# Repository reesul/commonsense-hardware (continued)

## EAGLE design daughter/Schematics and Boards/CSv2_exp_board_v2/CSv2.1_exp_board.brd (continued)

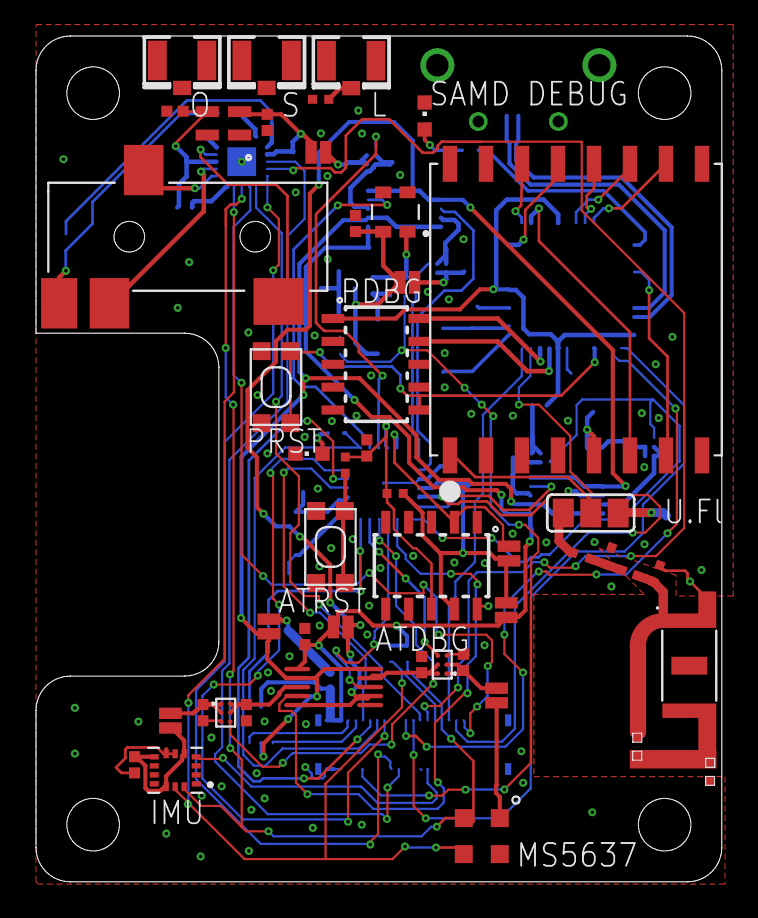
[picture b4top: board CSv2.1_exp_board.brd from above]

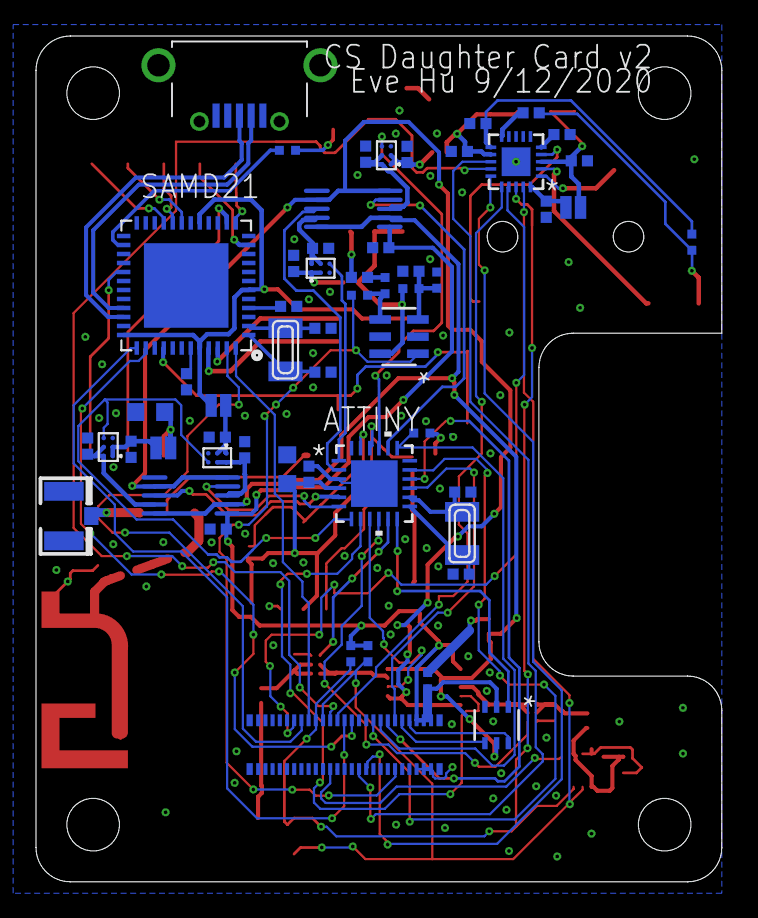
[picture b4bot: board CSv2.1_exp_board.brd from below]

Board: 2 copper layers, 38.1 x 47.0 mm, 103 parts (56 on the bottom side), 98 nets.

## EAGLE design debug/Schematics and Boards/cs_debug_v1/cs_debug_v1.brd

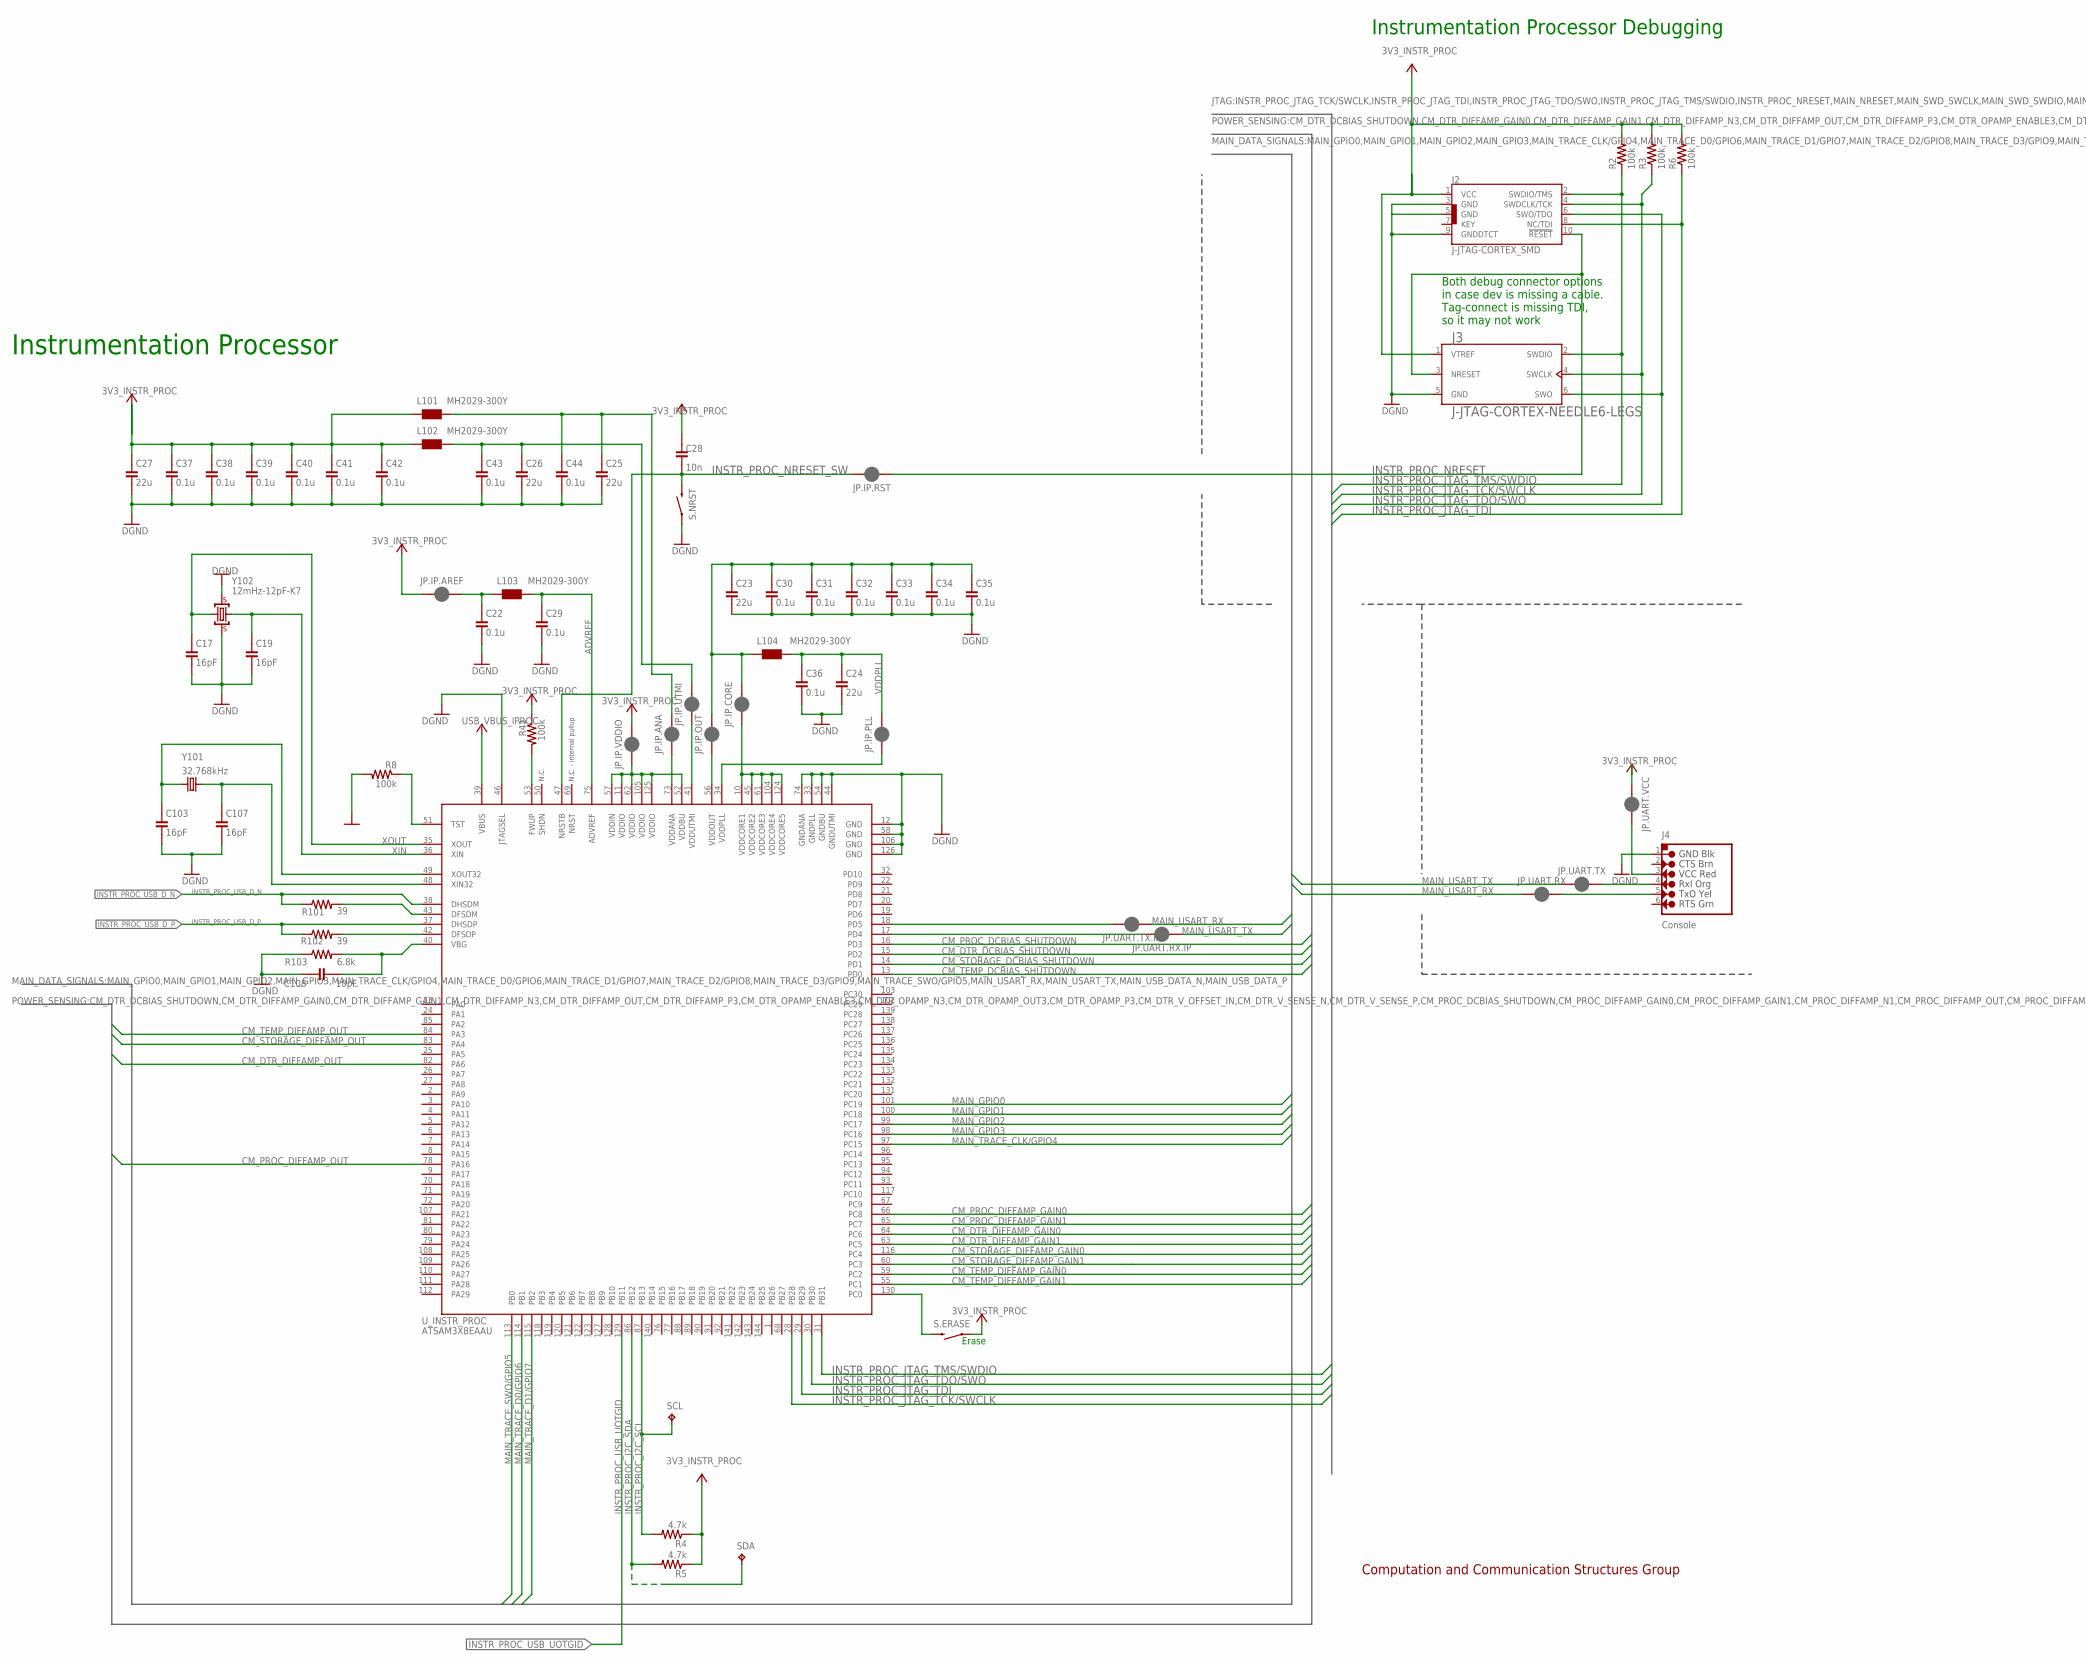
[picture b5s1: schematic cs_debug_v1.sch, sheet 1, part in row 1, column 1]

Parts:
C17, C19, C103, C107: 16pF; C0603; MPN C0603C160J5GACTU
C22, C29, C30, C31, C32, C33, C34, C35, C36, C37, C38, C39, C40, C41, C42, C43, C44: 0.1u; C0402; VOLTAGE 10V; MPN C0402C104K8RACTU
C23, C24, C25, C26, C27: 22u; C0805; VOLTAGE 10V; MPN C0805C226M8PAC7800
C28: 10n; C0402; MPN C0402C103K8RACTU
C108: 10pF; C0603; MPN C0603C100K8RAC7867
J2: J-JTAG-CORTEX_SMD; SAMTECH_FTSH-105-01; PART_NO FTSH-105-01-L-DV-K-TR
J3: J-JTAG-CORTEX-NEEDLE6-LEGS; 8.06.16_6-PIN_NEEDLE_ADAPTER_LEGS
J4: J-SERIAL-PORT; HEADER-1X6; PART_NO PH1-06-UA
JP.IP.ANA, JP.IP.AREF, JP.IP.CORE, JP.IP.OUT, JP.IP.PLL, JP.IP.RST, JP.IP.UTMI, JP.IP.VDDIO, JP.UART.RX, JP.UART.RX.IP, JP.UART.TX, JP.UART.TX.IP, JP.UART.VCC: JUMPER-SMT_2_NC_PASTE_NO-SILK; SMT-JUMPER_2_NC_PASTE_NO-SILK
L101, L102, L103, L104: MH2029-300Y; L0805; PART_NO MH2029-300Y
R2, R3, R6: 100k; R0402; MPN ERJ-2GEJ104X
R4, R5: 4.7k; R0402; MPN ERJ-2GEJ472X
R8, R41: 100k; R0402; MPN RC0402JR-07100KL
R101, R102: 39; R0402; MPN ERJ-2GEJ390X
R103: 6.8k; R0402; MPN ERJ-2GEJ682X
S.ERASE, S.NRST: Momentary; SW_EVQ-P7L01P; MPN EVQP7L01P
SCL: TPTP10SQ; TP10SQ
SDA: TPTP10SQ; TP10SQ
U_INSTR_PROC: ATSAM3X8EA-AU; LQFP144; MPN ATSAM3X8EAAU
Y101: 32.768kHz; CRYSTAL-SMD-3.2X1.5MM; MPN ECS-.327-12.5-34B-TR
Y102: 12mHz-12pF-K7; CRYSTAL-3.2-2.5; MPN ABM8G-12.000MHZ-4Y-T3

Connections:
3V3_INSTR_PROC: C27.1, C28.1, C37.1, C38.1, C39.1, C40.1, C41.1, C42.1, J2.1 (VCC), J3.1 (VTREF), JP.IP.AREF.1, JP.IP.VDDIO.2, JP.UART.VCC.1, L101.1, L102.1, R2.2, R3.2, R4.1, R5.1, R6.2, R41.1, S.ERASE.1_1 (1), S.ERASE.1_2 (1); also elsewhere on the board
ADVREF: C29.1, L103.2, U_INSTR_PROC.75 (ADVREF)
ADVREF_PRE: C22.1, JP.IP.AREF.2, L103.1
CM_DTR_DCBIAS_SHUTDOWN: U_INSTR_PROC.15 (PD2); also elsewhere on the board
CM_DTR_DIFFAMP_GAIN0: U_INSTR_PROC.64 (PC6); also elsewhere on the board
CM_DTR_DIFFAMP_GAIN1: U_INSTR_PROC.63 (PC5); also elsewhere on the board
CM_DTR_DIFFAMP_OUT: U_INSTR_PROC.82 (PA6); also elsewhere on the board
CM_PROC_DCBIAS_SHUTDOWN: U_INSTR_PROC.16 (PD3); also elsewhere on the board
CM_PROC_DIFFAMP_GAIN0: U_INSTR_PROC.66 (PC8); also elsewhere on the board
CM_PROC_DIFFAMP_GAIN1: U_INSTR_PROC.65 (PC7); also elsewhere on the board
CM_PROC_DIFFAMP_OUT: U_INSTR_PROC.78 (PA16); also elsewhere on the board
CM_STORAGE_DCBIAS_SHUTDOWN: U_INSTR_PROC.14 (PD1); also elsewhere on the board
CM_STORAGE_DIFFAMP_GAIN0: U_INSTR_PROC.116 (PC4); also elsewhere on the board
CM_STORAGE_DIFFAMP_GAIN1: U_INSTR_PROC.60 (PC3); also elsewhere on the board
CM_STORAGE_DIFFAMP_OUT: U_INSTR_PROC.83 (PA4); also elsewhere on the board
CM_TEMP_DCBIAS_SHUTDOWN: U_INSTR_PROC.13 (PD0); also elsewhere on the board
CM_TEMP_DIFFAMP_GAIN0: U_INSTR_PROC.59 (PC2); also elsewhere on the board
CM_TEMP_DIFFAMP_GAIN1: U_INSTR_PROC.55 (PC1); also elsewhere on the board
CM_TEMP_DIFFAMP_OUT: U_INSTR_PROC.84 (PA3); also elsewhere on the board
DGND: C17.2, C19.2, C22.2, C23.2, C24.2, C25.2, C26.2, C27.2, C29.2, C30.2, C31.2, C32.2, C33.2, C34.2, C35.2, C36.2, C37.2, C38.2, C39.2, C40.2, C41.2, C42.2, C43.2, C44.2, C103.2, C107.2, C108.2, J2.3 (GND), J2.5 (GND), J2.9 (GNDDTCT), J3.5 (GND), J4.1 (GND), R8.2, R103.1, S.NRST.1_1 (1), S.NRST.1_2 (1), U_INSTR_PROC.12 (GND), U_INSTR_PROC.33 (GNDPLL), U_INSTR_PROC.44 (GNDUTMI), U_INSTR_PROC.46 (JTAGSEL), U_INSTR_PROC.54 (GNDBU), U_INSTR_PROC.58 (GND), U_INSTR_PROC.74 (GNDANA), U_INSTR_PROC.106 (GND), U_INSTR_PROC.126 (GND), Y102.2 (GND), Y102.4 (GND); also elsewhere on the board
ERASE_S: S.ERASE.2_1 (2), S.ERASE.2_2 (2), U_INSTR_PROC.130 (PC0)
FWUP: R41.2, U_INSTR_PROC.53 (FWUP)
INSTR_PROC_I2C_SCL: R4.2, SCL.TP, U_INSTR_PROC.87 (PB13); also elsewhere on the board
INSTR_PROC_I2C_SDA: R5.2, SDA.TP, U_INSTR_PROC.86 (PB12); also elsewhere on the board
INSTR_PROC_JTAG_TCK/SWCLK: J2.4 (SWDCLK/TCK), J3.4 (SWCLK), R3.1, U_INSTR_PROC.28 (PB28)
INSTR_PROC_JTAG_TDI: J2.8 (NC/TDI), R6.1, U_INSTR_PROC.29 (PB29)
INSTR_PROC_JTAG_TDO/SWO: J2.6 (SWO/TDO), J3.6 (SWO), U_INSTR_PROC.30 (PB30)
INSTR_PROC_JTAG_TMS/SWDIO: J2.2 (SWDIO/TMS), J3.2 (SWDIO), R2.1, U_INSTR_PROC.31 (PB31)
INSTR_PROC_NRESET: J2.10 (!RESET), J3.3 (NRESET), JP.IP.RST.1
INSTR_PROC_NRESET_SW: C28.2, JP.IP.RST.2, S.NRST.2_1 (2), S.NRST.2_2 (2), U_INSTR_PROC.47 (NRSTB)
INSTR_PROC_USB_D_N: R101.1, U_INSTR_PROC.38 (DHSDM); also elsewhere on the board
INSTR_PROC_USB_D_P: R102.1, U_INSTR_PROC.37 (DHSDP); also elsewhere on the board
INSTR_PROC_USB_UOTGID: U_INSTR_PROC.129 (PB11)
MAIN_GPIO0: U_INSTR_PROC.101 (PC19); also elsewhere on the board
MAIN_GPIO1: U_INSTR_PROC.100 (PC18); also elsewhere on the board
MAIN_GPIO2: U_INSTR_PROC.99 (PC17); also elsewhere on the board
MAIN_GPIO3: U_INSTR_PROC.98 (PC16); also elsewhere on the board
MAIN_TRACE_CLK/GPIO4: U_INSTR_PROC.97 (PC15); also elsewhere on the board
MAIN_TRACE_D0/GPIO6: U_INSTR_PROC.114 (PB1); also elsewhere on the board
MAIN_TRACE_D1/GPIO7: U_INSTR_PROC.115 (PB2); also elsewhere on the board
MAIN_TRACE_SWO/GPIO5: U_INSTR_PROC.113 (PB0); also elsewhere on the board
MAIN_USART_RX: JP.UART.RX.1, JP.UART.TX.IP.1; also elsewhere on the board
MAIN_USART_TX: JP.UART.RX.IP.1, JP.UART.TX.1; also elsewhere on the board
unnamed: R102.2, U_INSTR_PROC.42 (DFSDP)
unnamed: JP.UART.TX.IP.2, U_INSTR_PROC.18 (PD5)
unnamed: JP.UART.RX.IP.2, U_INSTR_PROC.17 (PD4)
unnamed: J4.4 (RX-I), JP.UART.TX.2
unnamed: J4.5 (TX-O), JP.UART.RX.2
unnamed: J4.3 (VCC-I), JP.UART.VCC.2
unnamed: R101.2, U_INSTR_PROC.43 (DFSDM)
TST: R8.1, U_INSTR_PROC.51 (TST)
USB_VBUS_IPROC: U_INSTR_PROC.39 (VBUS); also elsewhere on the board
VBG: C108.1, R103.2, U_INSTR_PROC.40 (VBG)
VDDANA1: C25.1, C44.1, JP.IP.ANA.2, L101.2
VDDANA_0: JP.IP.ANA.1, U_INSTR_PROC.73 (VDDANA)
VDDIO1: JP.IP.VDDIO.1, U_INSTR_PROC.11 (VDDIO), U_INSTR_PROC.52 (VDDBU), U_INSTR_PROC.57 (VDDIN), U_INSTR_PROC.62 (VDDIO), U_INSTR_PROC.105 (VDDIO), U_INSTR_PROC.125 (VDDIO)
VDDOUT: C23.1, C30.1, C31.1, C32.1, C33.1, C34.1, C35.1, JP.IP.CORE.2, JP.IP.OUT.2, L104.1
VDDOUTMI: C26.1, C43.1, JP.IP.UTMI.2, L102.2
VDDOUTMI_0: JP.IP.UTMI.1, U_INSTR_PROC.41 (VDDUTMI)
VDDOUT_0: JP.IP.OUT.1, U_INSTR_PROC.56 (VDDOUT)
VDDOUT_1: JP.IP.CORE.1, U_INSTR_PROC.10 (VDDCORE1), U_INSTR_PROC.45 (VDDCORE2), U_INSTR_PROC.61 (VDDCORE3), U_INSTR_PROC.104 (VDDCORE4), U_INSTR_PROC.124 (VDDCORE5)
VDDPLL: C24.1, C36.1, JP.IP.PLL.2, L104.2
VDDPLL_0: JP.IP.PLL.1, U_INSTR_PROC.34 (VDDPLL)
XIN: C19.1, U_INSTR_PROC.36 (XIN), Y102.1 (C1)
XIN32: C107.1, U_INSTR_PROC.48 (XIN32), Y101.P$1 (1)
XOUT: C17.1, U_INSTR_PROC.35 (XOUT), Y102.3 (C2)
XOUT32: C103.1, U_INSTR_PROC.49 (XOUT32), Y101.P$2 (2)

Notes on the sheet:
N.C.
N.C. - internal pullup
Instrumentation Processor
Computation and Communication Structures Group
Both debug connector options in case dev is missing a cable. Tag-connect is missing TDI, so it may not work
Instrumentation Processor Debugging
Erase

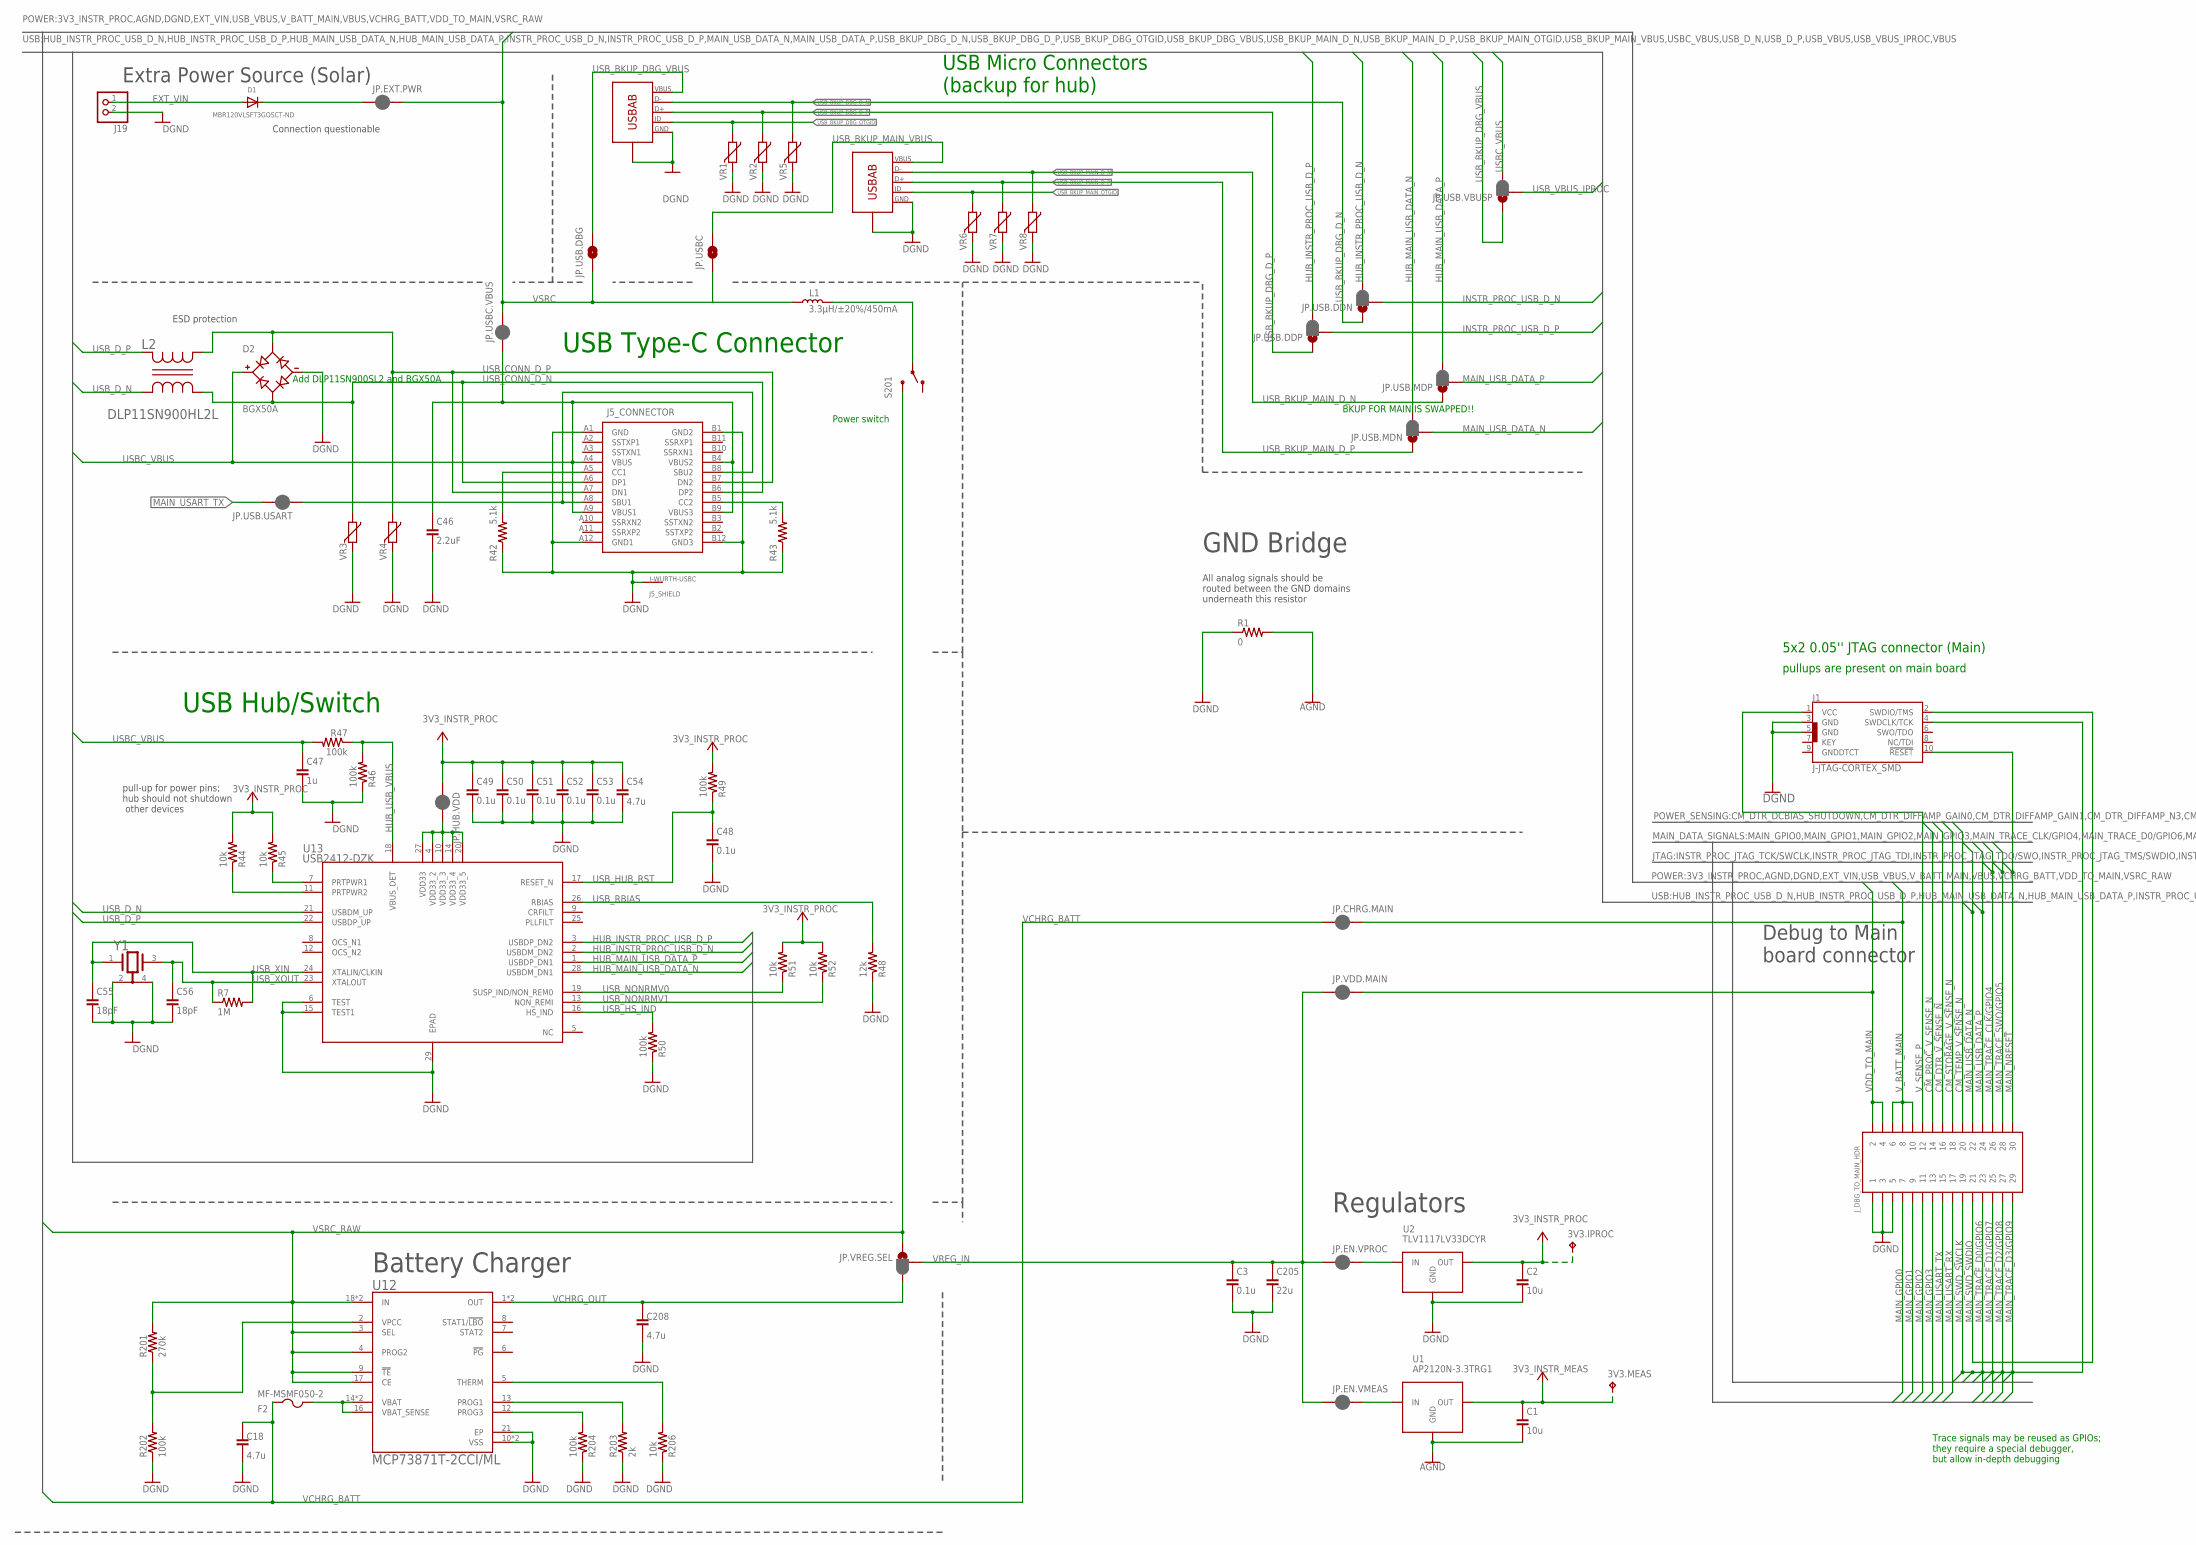
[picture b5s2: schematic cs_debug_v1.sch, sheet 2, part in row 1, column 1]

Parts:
3V3.IPROC, 3V3.MEAS: TPTP10SQ; TP10SQ
C1, C2: 10u; C0805; VOLTAGE 10V; MPN C0805C106M8RACTU
C3, C48, C49, C50, C51, C52, C53: 0.1u; C0402; VOLTAGE 10V; MPN C0402C104K8RACTU
C18, C54: 4.7u; C0402; MPN C0603C475M8PACTU
C46: 2.2uF; C0603; MPN C0603C225K8RACTU
C47: 1u; C0402; VOLTAGE 10V; MPN C0402C105K8PACTU
C55, C56: 18pF; C0402; MPN C0402C180J8GAC7867
C205: 22u; C0805; VOLTAGE 10V; MPN C0805C226M8PAC7800
C208: 4.7u; C0603; MPN C0603C475M8PACTU
D1: MBR120VLSFT3GOSCT-ND; SOD-123; MPN MBR120VLSFT3G
D2: BGX50A; SOT143_BGX50A
F2: MF-MSMF050-2; 1812; MPN MF-MSMF050-2
J1: J-JTAG-CORTEX_SMD; SAMTECH_FTSH-105-01; PART_NO FTSH-105-01-L-DV-K-TR
J5: J-WURTH-USBC; 632723X00011; PART_NO 632723100011
J19: Solar; JST-PH-2-SMT-RA; PART_NO S2B-PH-SM4-TB(LF)(SN)
J.USB.DBG, J.USB.MN: J-USB-HIROSE-MICRO-USB; USB-THRU-ZX62D-AB-5P8; MPN ZX62D-AB-5P8(30)
JP.CHRG.MAIN, JP.EN.VMEAS, JP.EN.VPROC, JP.EXT.PWR, JP.HUB.VDD, JP.USB.USART, JP.USBC.VBUS, JP.VDD.MAIN: JUMPER-SMT_2_NC_PASTE_NO-SILK; SMT-JUMPER_2_NC_PASTE_NO-SILK
JP.USB.DBG, JP.USBC: JUMPER-SMT_2_NO_PASTEFREE; SMT-JUMPER_2_NO_PASTEFREE_NO-SILK
JP.USB.DDN, JP.USB.DDP, JP.USB.MDN, JP.USB.MDP, JP.USB.VBUSP, JP.VREG.SEL: JUMPER-SMT_3_1-NC_PASTE_NO-SILK; SMT-JUMPER_3_1-NC_PASTE_NO-SILK
J_DBG_TO_MAIN_HDR: HIROSE-DF40_30-PIN_CONNECTORS-HEADER; HRS_DF40C-30DP-0.4V(51); MPN DF40C-30DP-0.4V(51)
L1: 3.3µH/±20%/450mA; 0805; MPN MLZ2012A3R3WT000
L2: DLP11SN900HL2L; IND_DLP11S_0504_MUR; MPN DLP11SN900HL2L
R1: 0; R2010; MPN ERJ-S1D0R00U
R7: 1M; R0402; MPN ERJ-U02J105X
R42, R43: 5.1k; R0603; MPN ERJ-3EKF5101V
R44, R45, R51, R52, R206: 10k; R0402; MPN ERJ-2GEJ103X
R46, R47, R49, R50, R202, R204: 100k; R0402; MPN ERJ-2GEJ104X
R48: 12k; R0402; MPN ERJ-2RKF1202X
R201: 270k; R0402; MPN ERJ-2GEJ274X
R203: 2k; R0402; MPN ERJ-2GEJ202X
S201: SLIDESWITCH-SPDT-SMD-RIGHT-ANGLE; SWITCH_SPST_SMD_A; PART_NO CUS-12TB
U1: AP2120N-3.3TRG1; SOT23-3_AP2120N; MPN AP2120N-3.3TRG1
U2: TLV1117LV33DCYR; DCY4
U12: MCP73871T-2CCI/ML; QFN50P400X400X100-21N; MPN MCP73871T-2CCI/ML
U13: USB2412-DZK; QFN28_5X5MC_MCH
VR1, VR2, VR3, VR4, VR5, VR6, VR7, VR8: VARISTOR; R0603; PART_NO CG0603MLC-05E
Y1: EPSON_TSX-3225_24.0000MF10Z-C3; XTAL_EPSON_TSX3225; MPN TSX-3225 24.0000MF10Z-C3

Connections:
3V3_INSTR_MEAS: 3V3.MEAS.TP, C1.1, U1.OUT; also elsewhere on the board
3V3_INSTR_PROC: 3V3.IPROC.TP, C2.1, C49.1, C50.1, C51.1, C52.1, C53.1, C54.1, JP.HUB.VDD.1, R44.2, R45.2, R49.2, R51.2, R52.2, U2.OUT, U2.OUT_TAB (OUT); also elsewhere on the board
AGND: C1.2, R1.2, U1.GND; also elsewhere on the board
BAT_CHG_PROG1: R203.2, U12.13 (PROG1)
CC3: J5.A5 (CC1), R42.2
CC4: J5.B5 (CC2), R43.2
CHG_VPCC: R201.1, R202.2, U12.2 (VPCC)
CM_DTR_V_SENSE_N: J_DBG_TO_MAIN_HDR.16; also elsewhere on the board
CM_PROC_V_SENSE_N: J_DBG_TO_MAIN_HDR.14; also elsewhere on the board
CM_STORAGE_V_SENSE_N: J_DBG_TO_MAIN_HDR.18; also elsewhere on the board
CM_TEMP_V_SENSE_N: J_DBG_TO_MAIN_HDR.20; also elsewhere on the board
DGND: C2.2, C3.2, C18.2, C46.2, C47.2, C48.2, C49.2, C50.2, C51.2, C52.2, C53.2, C54.2, C55.2, C56.2, C205.2, C208.2, D2.3 (-), J1.3 (GND), J1.5 (GND), J5.A1 (GND), J5.A12 (GND1), J5.B1 (GND2), J5.B12 (GND3), J5.GND (SHIELD), J5.GND1 (SHIELD), J5.Z1 (SHIELD), J5.Z2 (SHIELD), J5.Z3 (SHIELD), J5.Z4 (SHIELD), J5.Z5 (SHIELD), J5.Z6 (SHIELD), J19.2 (1), J.USB.DBG.GND, J.USB.DBG.S1 (SHIELD), J.USB.DBG.S2 (SHIELD), J.USB.DBG.S3 (SHIELD), J.USB.DBG.S4 (SHIELD), J.USB.MN.GND, J.USB.MN.S1 (SHIELD), J.USB.MN.S2 (SHIELD), J.USB.MN.S3 (SHIELD), J.USB.MN.S4 (SHIELD), J_DBG_TO_MAIN_HDR.1, J_DBG_TO_MAIN_HDR.3, J_DBG_TO_MAIN_HDR.5, R1.1, R42.1, R43.1, R46.1, R48.1, R50.1, R202.1, R203.1, R204.1, R206.1, U2.GND, U12.10 (VSS), U12.11 (VSS), U12.21 (EP), U13.6 (TEST), U13.15 (TEST1), U13.29 (EPAD), VR1.2, VR2.2, VR3.2, VR4.2, VR5.2, VR6.2, VR7.2, VR8.2, Y1.2 (1_GND), Y1.4 (2_GND); also elsewhere on the board
EXT_VIN: D1.A, J19.1 (2)
HUB_INSTR_PROC_USB_D_N: JP.USB.DDN.3, U13.2 (USBDM_DN2)
HUB_INSTR_PROC_USB_D_P: JP.USB.DDP.3, U13.3 (USBDP_DN2)
HUB_MAIN_USB_DATA_N: JP.USB.MDN.3, U13.28 (USBDM_DN1)
HUB_MAIN_USB_DATA_P: JP.USB.MDP.3, U13.1 (USBDP_DN1)
HUB_USB_VBUS: R46.2, R47.1, U13.18 (VBUS_DET)
INSTR_PROC_USB_D_N: JP.USB.DDN.2; also elsewhere on the board
INSTR_PROC_USB_D_P: JP.USB.DDP.2; also elsewhere on the board
MAIN_GPIO0: J_DBG_TO_MAIN_HDR.7; also elsewhere on the board
MAIN_GPIO1: J_DBG_TO_MAIN_HDR.9; also elsewhere on the board
MAIN_GPIO2: J_DBG_TO_MAIN_HDR.11; also elsewhere on the board
MAIN_GPIO3: J_DBG_TO_MAIN_HDR.13; also elsewhere on the board
MAIN_NRESET: J1.10 (!RESET), J_DBG_TO_MAIN_HDR.30
MAIN_SWD_SWCLK: J1.4 (SWDCLK/TCK), J_DBG_TO_MAIN_HDR.19
MAIN_SWD_SWDIO: J1.2 (SWDIO/TMS), J_DBG_TO_MAIN_HDR.21
MAIN_TRACE_CLK/GPIO4: J_DBG_TO_MAIN_HDR.26; also elsewhere on the board
MAIN_TRACE_D0/GPIO6: J_DBG_TO_MAIN_HDR.23; also elsewhere on the board
MAIN_TRACE_D1/GPIO7: J_DBG_TO_MAIN_HDR.25; also elsewhere on the board
MAIN_TRACE_D2/GPIO8: J_DBG_TO_MAIN_HDR.27
MAIN_TRACE_D3/GPIO9: J_DBG_TO_MAIN_HDR.29
MAIN_TRACE_SWO/GPIO5: J_DBG_TO_MAIN_HDR.28; also elsewhere on the board
MAIN_USART_RX: J_DBG_TO_MAIN_HDR.17; also elsewhere on the board
MAIN_USART_TX: JP.USB.USART.2, J_DBG_TO_MAIN_HDR.15; also elsewhere on the board
MAIN_USB_DATA_N: JP.USB.MDN.2, J_DBG_TO_MAIN_HDR.22
MAIN_USB_DATA_P: JP.USB.MDP.2, J_DBG_TO_MAIN_HDR.24
unnamed: JP.EN.VMEAS.2, U1.IN
unnamed: JP.EN.VPROC.2, U2.IN
unnamed: L1.2, S201.2
unnamed: F2.2, U12.14 (VBAT), U12.15 (VBAT), U12.16 (VBAT_SENSE)
unnamed: R204.2, U12.12 (PROG3)
unnamed: R45.1, U13.7 (PRTPWR1)
unnamed: D1.C, JP.EXT.PWR.1
unnamed: R44.1, U13.11 (PRTPWR2)
THERM: R206.2, U12.5 (THERM)
UCTX_DBGRX: J5.A8 (SBU1), J5.B8 (SBU2), JP.USB.USART.1
USBC_VBUS: C46.1, C47.1, D2.1 (+), J5.A4 (VBUS), J5.A9 (VBUS1), J5.B4 (VBUS2), J5.B9 (VBUS3), JP.USB.VBUSP.3, JP.USBC.VBUS.1, R47.2
USB_BKUP_DBG_D_N: J.USB.DBG.D-, JP.USB.DDN.1, VR5.1
USB_BKUP_DBG_D_P: J.USB.DBG.D+, JP.USB.DDP.1, VR2.1
USB_BKUP_DBG_OTGID: J.USB.DBG.USBID, VR1.1
USB_BKUP_DBG_VBUS: J.USB.DBG.VBUS, JP.USB.DBG.2, JP.USB.VBUSP.1
USB_BKUP_MAIN_D_N: J.USB.MN.D-, JP.USB.MDP.1, VR8.1
USB_BKUP_MAIN_D_P: J.USB.MN.D+, JP.USB.MDN.1, VR7.1
USB_BKUP_MAIN_OTGID: J.USB.MN.USBID, VR6.1
USB_BKUP_MAIN_VBUS: J.USB.MN.VBUS, JP.USBC.2
USB_CONN_D_N: D2.2 (AC1), J5.A6 (DP1), J5.B6 (DP2), L2.3, VR3.1
USB_CONN_D_P: D2.4 (AC2), J5.A7 (DN1), J5.B7 (DN2), L2.2, VR4.1
USB_D_N: L2.4, U13.21 (USBDM_UP)
USB_D_P: L2.1, U13.22 (USBDP_UP)
USB_HS_IND: R50.2, U13.16 (HS_IND)
USB_HUB_RST: C48.1, R49.1, U13.17 (RESET_N)
USB_HUB_VDD: JP.HUB.VDD.2, U13.4 (VDD33_2), U13.10 (VDD33_3), U13.14 (VDD33_4), U13.20 (VDD33_5), U13.27 (VDD33)
USB_NONRMV0: R51.1, U13.19 (SUSP_IND/NON_REM0)
USB_NONRMV1: R52.1, U13.13 (NON_REMI)
USB_RBIAS: R48.2, U13.26 (RBIAS)
USB_VBUS_IPROC: JP.USB.VBUSP.2; also elsewhere on the board
USB_XIN: C55.1, R7.2, U13.24 (XTALIN/CLKIN), Y1.1
USB_XOUT: C56.1, R7.1, U13.23 (XTALOUT), Y1.3
VCHRG_BATT: C18.1, F2.1, JP.CHRG.MAIN.1
VCHRG_OUT: C208.1, JP.VREG.SEL.3, U12.1 (OUT), U12.20 (OUT)
VDD_TO_MAIN: JP.VDD.MAIN.2, J_DBG_TO_MAIN_HDR.2, J_DBG_TO_MAIN_HDR.4
VREG_IN: C3.1, C205.1, JP.EN.VMEAS.1, JP.EN.VPROC.1, JP.VDD.MAIN.1, JP.VREG.SEL.2
VSRC: JP.EXT.PWR.2, JP.USB.DBG.1, JP.USBC.1, JP.USBC.VBUS.2, L1.1
VSRC_RAW: JP.VREG.SEL.1, R201.2, S201.3 (S), U12.3 (SEL), U12.4 (PROG2), U12.9 (!TE), U12.17 (CE), U12.18 (IN), U12.19 (IN)
V_BATT_MAIN: JP.CHRG.MAIN.2, J_DBG_TO_MAIN_HDR.6, J_DBG_TO_MAIN_HDR.8, J_DBG_TO_MAIN_HDR.10
V_SENSE_P: J1.1 (VCC), J_DBG_TO_MAIN_HDR.12; also elsewhere on the board

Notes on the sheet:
Debug to Main board connector
Trace signals may be reused as GPIOs; they require a special debugger, but allow in-depth debugging
All analog signals should be routed between the GND domains underneath this resistor
5x2 0.05'' JTAG connector (Main)
pullups are present on main board
Battery Charger
Power switch
Extra Power Source (Solar)
Regulators
GND Bridge
Add DLP11SN900SL2 and BGX50A
pull-up for power pins; hub should not shutdown other devices
Connection questionable
USB Type-C Connector
ESD protection
USB Hub/Switch
USB Micro Connectors (backup for hub)
BKUP FOR MAIN IS SWAPPED!!

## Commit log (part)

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2020-02-08 Directory structure added
    Please put Eagle .sch and .brd files in the "Schematics and Boards" folders
2020-02-08 Add files from WDA F2019
    Adding designs and datasheets from CommonSense v1 design. Most of this is copied from that repo to fit new directory structure.
2020-02-28 Create base schematic, begin wiring proc
2020-02-29 Add caps for D51 power pins; add reset sw
    Added all necessary caps and inductors for the power connection of the processor.
    Also added the reset switch. Using a switch from the sparkfun libraries. Part was chosen based on size.
    All added parts are included with part numbers from Kemet (C), Panasonic (R), or whichever brand Atmel recommends (mostly for inductors)
2020-02-29 Start adding xtals. Loads not calculated, fast xtal added
2020-03-11 Add SD card parts, start on power subsystem
    SD card parts added, but not connected to processor. Began on power subsystem. Decided to go with buck boost convertor from maxim. A few TI parts seemed like decent alternatives because they actually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
2020-03-14 Add load switch, sense resistors, breakout headers, and comments
    Load switch for SD card.
    Sense resistors daughter card header, processor, and SD card.
    Added 80 and 30 pin receptacles to design for daughter and debug cards, respectively. Pin count is a guess for now.
    Comments for power subsystem. In particular, comments on sense resistors and charging circuit (residing on debug card).
2020-03-14 Remove 30-pin header temporarily -- bad footprint
2020-03-14 Add power source selection; clean up pwr subsystem
    Battery charger will not be on main board, so power source selection hardware needs to be here to provide regulator with correct input. Using p-channel mosfet and schottky diode w/ low reverse curren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
2020-03-14 Add indicator LEDs
    LEDs powered by processor, but the processor cannot handle that much. Need MOSFET whose gates are connected to processor
2020-03-17 Add a few solder jumpers and a few probe points
2020-03-20 Add debugger
    Add 6 pin debugger, as there's no benefit to using 10 pin whatsoever.
    Also looked into digital LEDs and added a few comments in that part of schematic.
2020-03-21 Wire up SERCOM 0-5 for daughter board, master 2c, & debug uart
2020-03-21 Processor wired up
2020-03-22 Wire up connectors. Schematic complete, awaiting review
2020-03-28 Placement for majority of board
    Board placement gives about 1.4x1.4inch board; under 2 sqin. SD card takes up substantial space, and connectors will need sufficient space for routing signals.
2020-04-04 Move CC after power selection. Add SPI flash over SD. Swap PowSel diode
2020-04-04 Minor sh changes; placed compressed power subsys, gitignore temp files
2020-04-04 Board placement for 1in x 1in. Unrouted
2020-04-05 Ready to route
    interior planes placed, but not exterior. Layering stackup setup similar to the way JLC recommends (hopefully standard)
2020-04-18 Updated stackup for 8-layer. Added feasible via pairs
    My understanding of viable via pairs is still a bit shaky (or at least what proto express can do). I have designed to have a few pairs of micro vias, and through hole plating for each core-to-core la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
2020-04-18 Setup DRU according to ProtoExpress for 8-layer HDI
2020-04-18 Re-place a few components and prep for routing
2020-04-18 Manual route power traces, lock traces/vias before autoroute
2020-04-19 Escape for BGA signals with microvia in pad
2020-04-20 Attempt to hand route signals; about 30% done w/ BGA
2020-04-21 All but DTR/DBG signals hand routed
2020-04-21 Passed with no DRC errors
2020-04-21 Add GND plugs
2020-04-21 Setup fill polygons
    Design complete (until manufacturer points out issues). About 500 vias... ouch
2020-04-25 Generate BOM, CAM files. Submitted to ProtoExpress for custom quote
    Expecting to have many updates to do to the board as part of the quote. Expecting cost to be in 4-5k range for a run of 5
2020-05-02 Layout for CSv2.0 as larger 4-layer proto board. Archived 8-layer layout
2020-05-02 Hand routed power traces, setup DRU
    Traces and vias unlocked. No ground planes; just fill.
    Most ground traces via'd to let fill easily handle them. Not sure if autoroute will try to route them on their own, but escaping there probably won't be sufficient fill w/i the BGA's area.
    DRU setup for 4mil traces, 6mil vias, no microvias
2020-05-02 Ready to route
2020-05-02 Avoided catastrophe from file inconsistencies
    Several hours of nightmare-inducing file-fiddling later...
2020-05-05 Routed last power traces, made polygon fills
    Most of the ground traces are just via'd so that GND fill can pick them up without more traces
2020-05-09 Add screw holes (4) for M2 screws. Adjust layout and some traces
2020-05-09 Hand route a handful of signals to non-connector parts
2020-05-09 Routed and GND-plugged
2020-05-09 Add BOMs
2020-05-09 Generate CAM, fix BOM, get quote
2020-05-09 Changed 1 part number. Included in BOM of previous commit
2020-05-14 Fix a few items based on 1st round DFM checks with 7pcb
2020-05-16 Adding item outlines to Eagle as part of DFM issues
2020-05-16 Add reference designators to each BOM part on board (tDocu layer)
2020-05-23 Add baseline files for debug card
    Most work to this end has been in planning the set of components, subsystems that will need to be present, as long as some considerations for physical layouts
2020-05-29 Rename a few pins to show which SERCOM port is used
2020-05-29 Add amplifiers and passives for high-side current monitor
    FETs still to be added. Haven't set values on passives or added any part numbers to the circuit. Still need to convert the whole thing into a group. The nets have been named, and a few notes left beh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
2020-05-30 Add high side current monitors as groups; label pins from main connector
2020-06-04 Add a few signals to DTR card connector
2020-06-04 Signals from instrumentation processor to current monitors
2020-06-06 Add debug connectors, DAC, pull-ups to schematic
2020-06-09 Finish first-pass of Debug Board schematic
2020-06-11 added data sheets and schematic v1
2020-06-11 Change USART Header on debug board
2020-06-11 Add USB connector and switch IC
2020-06-12 Add and name test points for debug board
2020-06-12 Organized daughter card data sheet folder
2020-06-12 Add backup micro-usb ports
2020-06-13 Relative subsystem placement
    still off board
2020-06-14 DTR-added test points, usb-c, and i2c pull-ups
2020-06-14 DTR-reorganized eagle folder
2020-06-16 DBG- begin board placement and routing
    Will create another branch for the many commits needed as part of routing
2020-06-16 DBG- layout and hand-route for current monitors
2020-06-16 DBG-routing for differential USB signals, update placements
2020-06-17 DBG- analog signals hand-routed to go under 0-ohm gnd bridge
    Some digital signals that went between planes were not routed under the bridge. There are the signals that shutdown the opamp that is doing offset biasing. The signals are at about 2 levels removed f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
2020-06-17 DBG- USB signals finished routing
    Differential pairs do wonky things as they try to get identical lengths. I probably violated some rules in this regard, but it should be pretty minimal. Worst offense is the use of 3-pad solder jumpe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
2020-06-17 DBG - autoroute 100%
2020-06-17 DBG- DRC errors resolved; due for one more review
2020-06-17 DBG-Manual checks & minor cleanup
2020-06-18 DTR-replacement and manual routing
2020-06-19 DTR-hand-routing continued
2020-06-19 DTR-routing 100% + DRC resolved
2020-06-19 DTR-added text/labels
2020-06-19 DBG-Cleanup Silkscreen
2020-06-19 DBG-rounded edges
2020-06-20 Add CAM/Gerbers, manage BOM, and make purchase.
2020-06-21 DTR-added three ufl connectors for rf calibratiion
2020-06-26 DTR-added codec datasheet and did replacement
2020-06-26 DTR-moved the chip antenna a bit further from the connector
2020-06-26 DTR-fixed keepout error
2020-06-28 DTR-added ldo and 80% manual routing
2020-06-29 DTR-drc resolved, schematic check, routing check
2020-07-01 DTR-filled in device specs and double checked the footprint consistency
2020-07-02 DTR-updated BOM
2020-07-02 DTR-filled in device attributes
2020-07-02 DTR-fixed sch-brd inconsistency problem
2020-07-02 DTR-v1.1 after moving LoRa to the top
2020-07-02 Add files for main 2.1, majority rip-up, modify placement, round corners
2020-07-11 Minor modifications from learnings of debug-board build
2020-08-04 Minor changes and notes
    Nothing fundamental changed here; mostly preparation for a round of revisions
2020-08-04 Revision 2.1 of schematic for the CommonSense Main Board
    Changes include (at the least): Removal LED NFETs, increase connector size to 50 pins w/ 4mm z-height, swap FLASH for a Winbond part with 1 Gbit NVM, change current measurement to include two daughte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
    These changes are local to the schematic, for the most part. Changes to the board are minimal, but do include shifting the connector up, as well as the top-most d
2020-08-05 Upgrade power selection on main board from PFET -> 2:1 power mux
    Testing on CSmain 2.0 showed some disturbing changes in voltage across the PFET (most likely due to an device physics imposing a typical Vgs threshold before conducting well) that would make the LDO 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
    Also included is a load switch whose enable is controlled by a mechanical switch. This should be more trustworthy than a PFET, and can conduct substantially more current than the mechanical switch al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
2020-08-05 Swap daughter card v-sense pins
2020-08-06 Finished schematic revision for main, debug boards.
2020-08-06 Route differential USB signals
2020-08-06 Edit silk and documentation layers for pick-and-place assembly
2020-08-06 Route minimal analog signals under ground bridge, add near ground plugs
2020-08-06 minor silk change
2020-08-07 CSv2.1 main board part placement; routing for power traces
2020-08-07 Move processor to make routing to connectors easier
2020-08-07 Re-jumble processor power traces and caps to make routing easier
2020-08-07 CS-main-v2.1 Routed to completion
    Still need to add ground plugs.
2020-08-07 Gerbers, BOM, and minor part changes
2020-08-07 Minor changes, BOM generation & formatting, CAM for debug
2020-08-18 dtrv2.1 manual routing
2020-08-23 DTRv2.1 finished routing
2020-08-28 DBG: move component from screw hole and regen gerbers
2020-08-28 DBG: Increase holes sizes for snap-lock inter-board connectors
2020-08-28 BASE: Increase holes sizes for snap-lock inter-board connectors
2020-09-01 DTR: increase hole sizes
2020-09-01 DBG: Replace bias resistors of current measurement w/ correct part
    And regenerate the CAM files.
2020-09-07 File mgmt for manufacture prep. Minor change to DTR board + gen gerbers
2020-09-08 Update minimum design rules: 5 mil trace/space & 0.2mm vias
    This is to aid manufacturability and decrease cost. <0.2mm vias is a large cost increase, especially.
    Traces were already 5mil, but DRC was checking for 4mil space
2020-09-08 Fixed all clearance issues for increased min trace/space/via sizes
2020-09-09 DTR: fixed all airwires
2020-09-09 DTR - fixed BOM
2020-09-09 DTR: regenerate CAM and format BOM for Octopart
2020-09-11 Update files per design review and regenerate CAM
2020-09-11 Minor part renaming per octopart BOM tool
2020-09-15 DTR-fixed silk screem and switched to a new pressure sensor
2020-09-15 DTR - added notes to the schematic
2020-09-15 STACK: Generate Gerbers, format BOM, manage directories
2020-09-22 DBG: Fix DFM issues for 7PCB
2020-09-22 DTR: update SGTL5000 library part according to the SDFM
2020-09-22 DTR: generate gerbers after DFM fixes
2020-10-30 DTR: Regen gerbers for final design fixes in rev2.1
